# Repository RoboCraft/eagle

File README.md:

# eagle
EAGLE library and projects

Links:
https://learn.sparkfun.com/tutorials/using-eagle-schematic
https://learn.sparkfun.com/tutorials/using-eagle-board-layout

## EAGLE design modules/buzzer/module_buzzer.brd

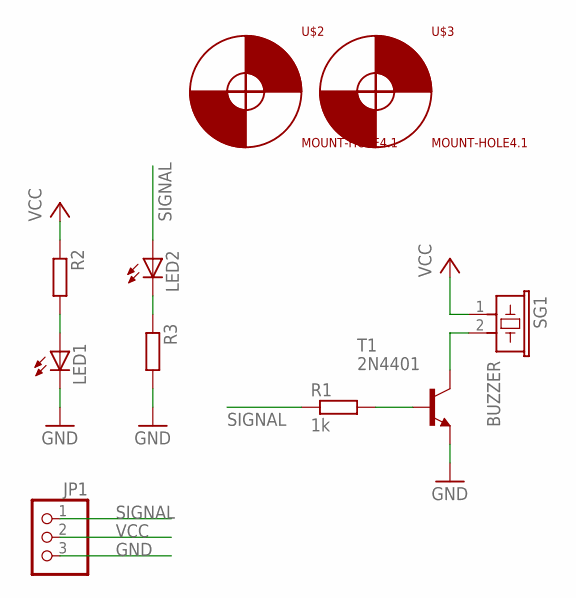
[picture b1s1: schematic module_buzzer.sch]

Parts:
JP1: PINHD-1X3; 1X03
LED1, LED2: LED5MM
R1: 1k; 0207/7
R2, R3: R-EU_0207_7; 0207/7
SG1: BUZZER; BUZZER-HCM1212A
T1: 2N4401; TO92-CBE
U$2, U$3: MOUNT-HOLE4.1; 4.1

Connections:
GND: JP1.3, LED1.K (C), R3.2, T1.E
unnamed: LED1.A, R2.2
unnamed: R1.2, T1.B
unnamed: SG1.2, T1.C
unnamed: LED2.K (C), R3.1
SIGNAL: JP1.1, LED2.A, R1.1
VCC: JP1.2, R2.1, SG1.1

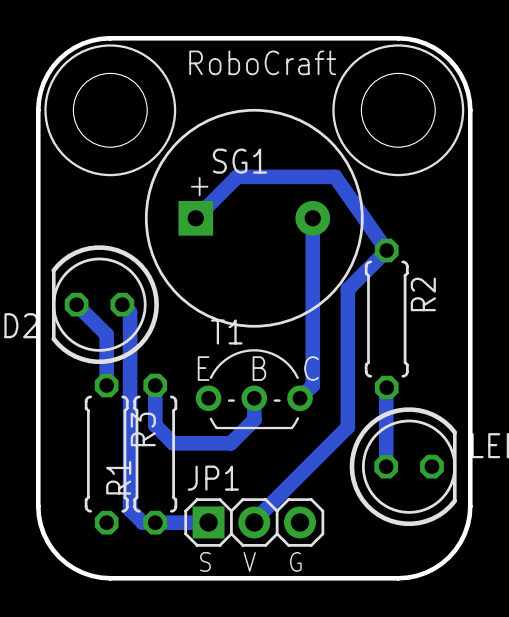
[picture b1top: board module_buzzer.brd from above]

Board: 2 copper layers, 24.0 x 30.0 mm, 10 parts (0 on the bottom side), 7 nets.

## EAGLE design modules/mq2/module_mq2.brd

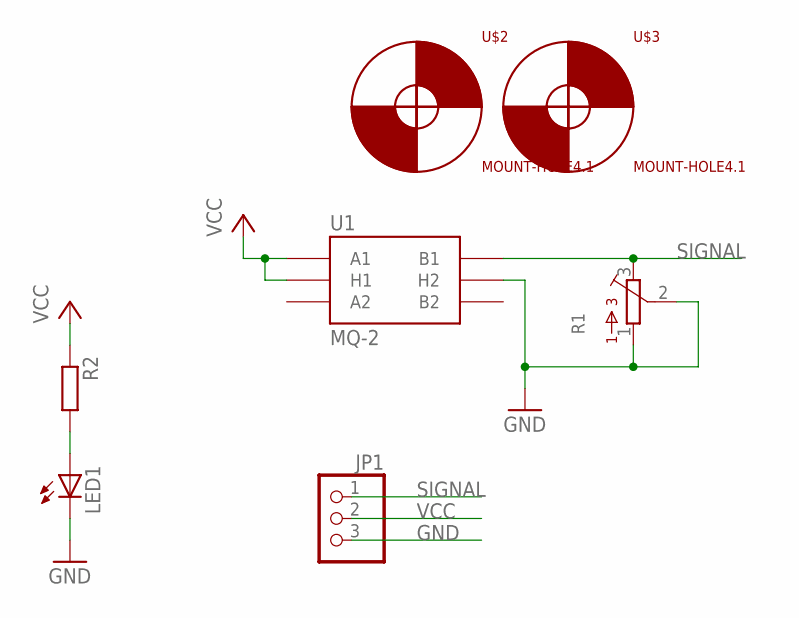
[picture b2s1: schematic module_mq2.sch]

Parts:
JP1: PINHD-1X3; 1X03
LED1: LED5MM
R1: 3386-P; 3386P
R2: R-EU_0207_7; 0207/7
U1: MQ-2
U$2, U$3: MOUNT-HOLE4.1; 4.1

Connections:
GND: JP1.3, LED1.K (C), R1.1, R1.2, U1.HB (H2)
unnamed: LED1.A, R2.2
SIGNAL: JP1.1, R1.3, U1.B1
VCC: JP1.2, R2.1, U1.A1, U1.HA (H1)

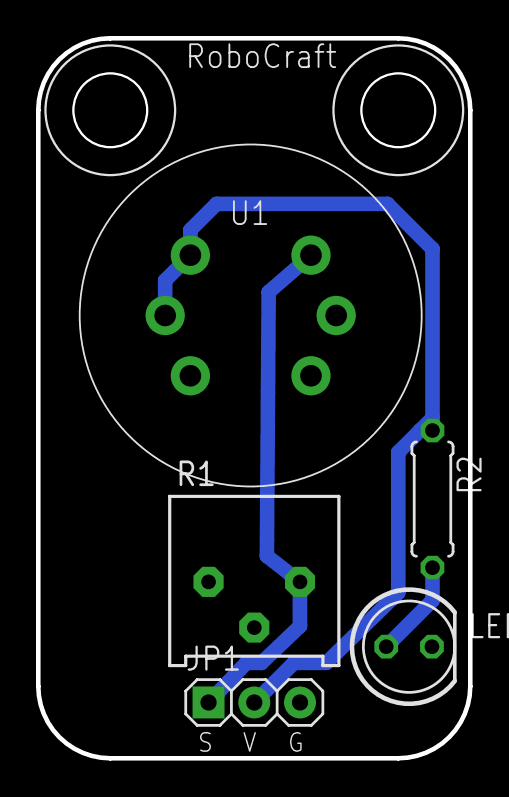
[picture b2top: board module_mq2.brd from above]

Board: 2 copper layers, 24.0 x 40.0 mm, 7 parts (0 on the bottom side), 4 nets.

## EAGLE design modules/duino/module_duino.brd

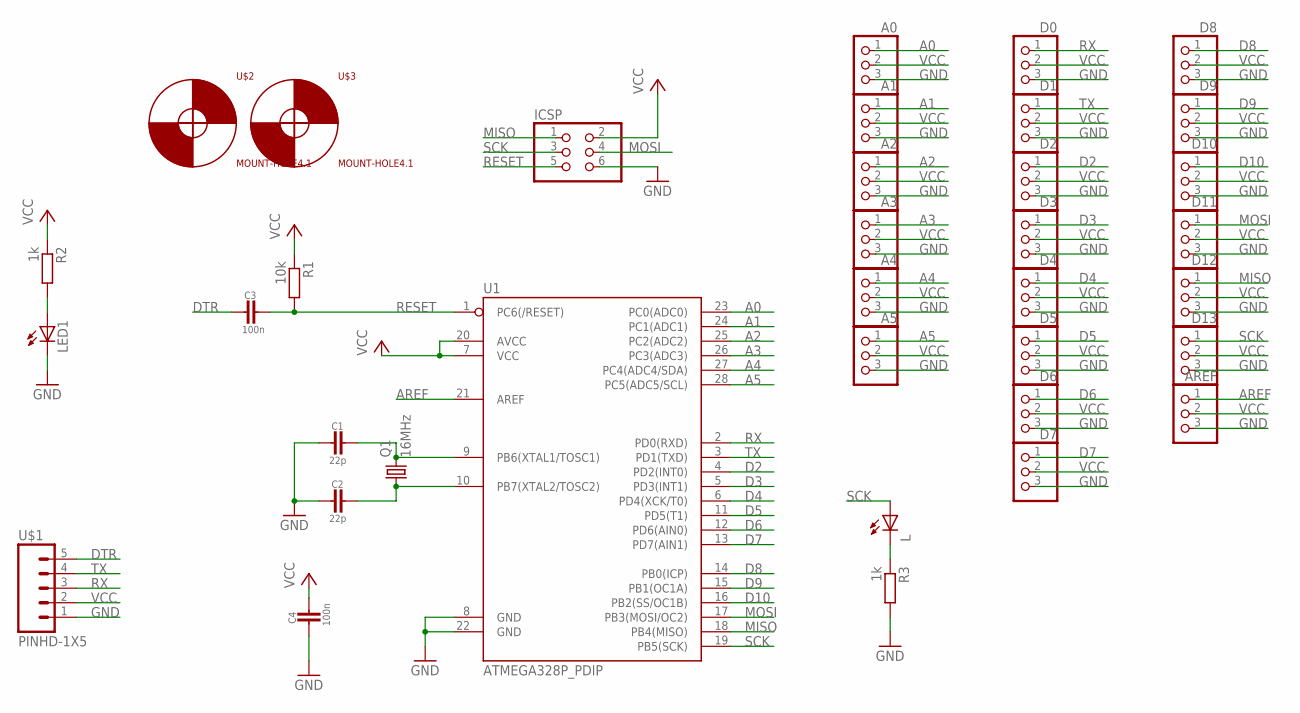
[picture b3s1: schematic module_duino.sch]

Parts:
A0, A1, A2, A3, A4, A5: PINHD-1X3; 1X03
AREF: PINHD-1X3; 1X03
C1, C2: 22p; CAP-PTH-5MM
C3, C4: 100n; CAP-PTH-5MM
D0, D1, D2, D3, D4, D5, D6, D7, D8, D9, D10, D11, D12, D13: PINHD-1X3; 1X03
ICSP: PINHD-2X3; 2X03
L: LED5MM
LED1: LED5MM
Q1: 16MHz; HC49/S
R1: 10k; 0207/7
R2, R3: 1k; 0207/7
U1: ATMEGA328P_PDIP; DIL28-3
U$1: PINHD-1X5; 1X05-CLEAN
U$2, U$3: MOUNT-HOLE4.1; 4.1

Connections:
A0: A0.1, U1.23 (PC0(ADC0))
A1: A1.1, U1.24 (PC1(ADC1))
A2: A2.1, U1.25 (PC2(ADC2))
A3: A3.1, U1.26 (PC3(ADC3))
A4: A4.1, U1.27 (PC4(ADC4/SDA))
A5: A5.1, U1.28 (PC5(ADC5/SCL))
AREF: AREF.1, U1.21 (AREF)
D2: D2.1, U1.4 (PD2(INT0))
D3: D3.1, U1.5 (PD3(INT1))
D4: D4.1, U1.6 (PD4(XCK/T0))
D5: D5.1, U1.11 (PD5(T1))
D6: D6.1, U1.12 (PD6(AIN0))
D7: D7.1, U1.13 (PD7(AIN1))
D8: D8.1, U1.14 (PB0(ICP))
D9: D9.1, U1.15 (PB1(OC1A))
D10: D10.1, U1.16 (PB2(SS/OC1B))
DTR: C3.1, U$1.5
GND: A0.3, A1.3, A2.3, A3.3, A4.3, A5.3, AREF.3, C1.1, C2.1, C4.1, D0.3, D1.3, D2.3, D3.3, D4.3, D5.3, D6.3, D7.3, D8.3, D9.3, D10.3, D11.3, D12.3, D13.3, ICSP.6, LED1.K (C), R3.2, U1.8 (GND), U1.22 (GND), U$1.1
MISO: D12.1, ICSP.1, U1.18 (PB4(MISO))
MOSI: D11.1, ICSP.4, U1.17 (PB3(MOSI/OC2))
unnamed: LED1.A, R2.2
unnamed: C1.2, Q1.2, U1.9 (PB6(XTAL1/TOSC1))
unnamed: C2.2, Q1.1, U1.10 (PB7(XTAL2/TOSC2))
unnamed: L.K (C), R3.1
RESET: C3.2, ICSP.5, R1.2, U1.1 (PC6(/RESET))
RX: D0.1, U1.2 (PD0(RXD)), U$1.3
SCK: D13.1, ICSP.3, L.A, U1.19 (PB5(SCK))
TX: D1.1, U1.3 (PD1(TXD)), U$1.4
VCC: A0.2, A1.2, A2.2, A3.2, A4.2, A5.2, AREF.2, C4.2, D0.2, D1.2, D2.2, D3.2, D4.2, D5.2, D6.2, D7.2, D8.2, D9.2, D10.2, D11.2, D12.2, D13.2, ICSP.2, R1.1, R2.1, U1.7 (VCC), U1.20 (AVCC), U$1.2

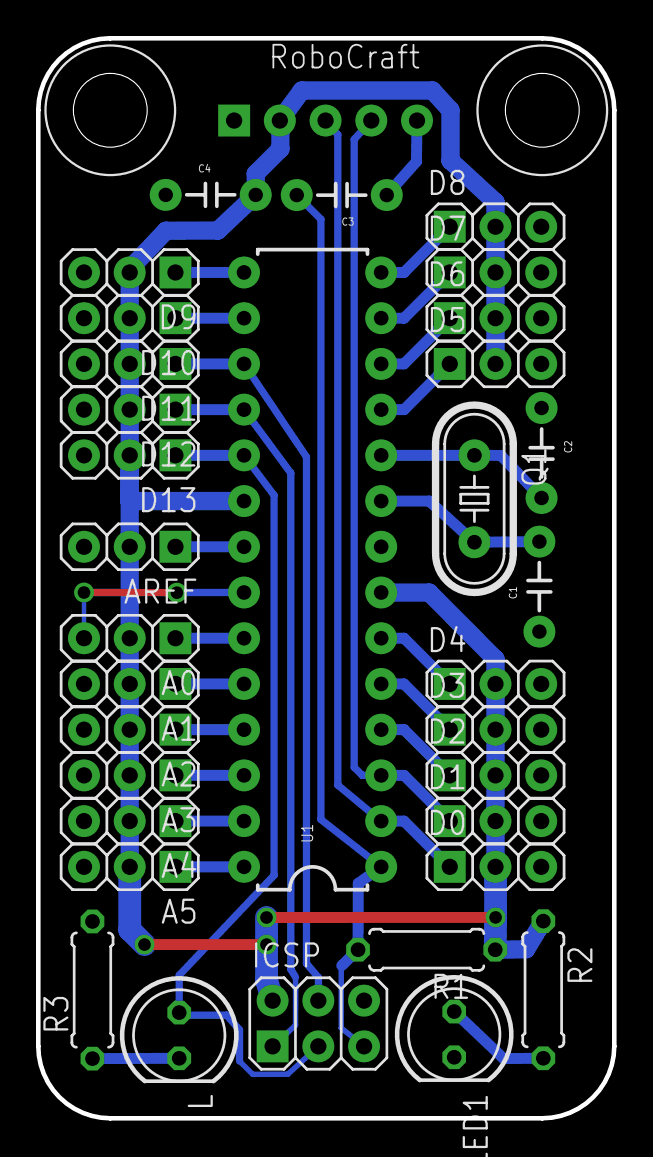
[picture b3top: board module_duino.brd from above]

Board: 2 copper layers, 32.0 x 60.0 mm, 36 parts (0 on the bottom side), 29 nets.

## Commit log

2015-02-24 add robocraft library and modules
2015-02-24 first
